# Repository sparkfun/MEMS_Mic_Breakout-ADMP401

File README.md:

**NOTE:** *This product has been retired from our catalog due to the IC being EOL. We recommend checking out the [ICS-40180](https://www.sparkfun.com/products/18011) as an alternative. While the ICS-40180 has similar characteristics, note that the footprint is different than the ADMP401. If you are looking for more up-to-date info, please check out the following resource to see how other users are still hacking and improving on this product.*

* *[SparkFun Forum](https://forum.sparkfun.com/)*

SparkFun MEMS Microphone Breakout - INMP401 (ADMP401)
===================================================

[*SparkFun MEMS Microphone Breakout - INMP401 (ADMP401) (BOB-09868)*](https://www.sparkfun.com/products/9868)

This tiny breakout board features the ADMP401 MEMs microphone.

Repository Contents
-------------------
* **/Firmware** - Example Arduino Sketches 
* **/Hardware** - All Eagle design files (.brd, .sch)

Documentation
--------------
* **[Hookup Guide](https://learn.sparkfun.com/tutorials/mems-microphone-hookup-guide)** - Basic hookup guide.

License Information
-------------------
The hardware is released under [Creative Commons ShareAlike 4.0 International](https://creativecommons.org/licenses/by-sa/4.0/).
The code is beerware; if you see me (or any other SparkFun employee) at the local, and you've found our code helpful, please buy us a round!

Distributed as-is; no warranty is given.

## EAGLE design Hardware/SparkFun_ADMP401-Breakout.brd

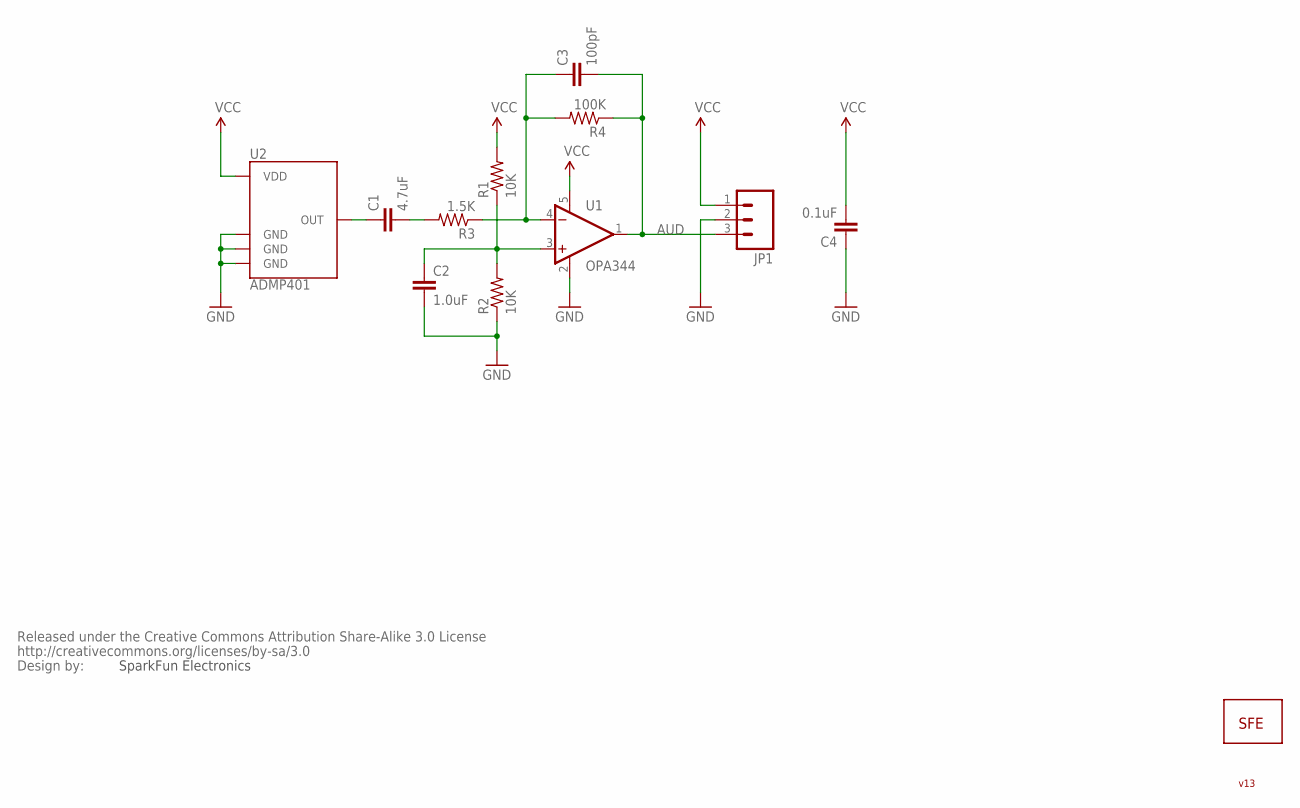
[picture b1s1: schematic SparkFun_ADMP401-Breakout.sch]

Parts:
C1: 4.7uF; 0402-CAP
C2: 1.0uF; 0402-CAP
C3: 100pF; 0402-CAP
C4: 0.1uF; 0402-CAP
JP1: M03PTH; 1X03
R1, R2: 10K; 0402-RES
R3: 1.5K; 0402-RES
R4: 100K; 0402-RES
U1: OPA344; SOT23-5
U2: ADMP401
U$1: LOGO-SFESK; SFE-LOGO-FLAME
U$2: CREATIVE_COMMONS

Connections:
AUD: C3.2, JP1.3, R4.1, U1.1 (OUT)
GND: C2.2, C4.1, JP1.2, R2.1, U1.2 (V-), U2.2 (GND), U2.4 (GND), U2.6 (GND)
unnamed: C1.1, U2.1 (OUT)
unnamed: C3.1, R3.1, R4.2, U1.4 (-IN)
unnamed: C1.2, R3.2
unnamed: C2.1, R1.1, R2.2, U1.3 (+IN)
VCC: C4.2, JP1.1, R1.2, U1.5 (V+), U2.5 (VDD)

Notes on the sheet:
SparkFun Electronics
v13

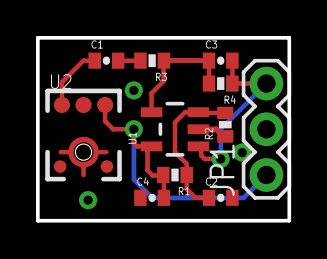
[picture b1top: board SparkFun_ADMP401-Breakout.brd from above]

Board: 2 copper layers, 14.0 x 10.2 mm, 13 parts (1 on the bottom side), 7 nets.

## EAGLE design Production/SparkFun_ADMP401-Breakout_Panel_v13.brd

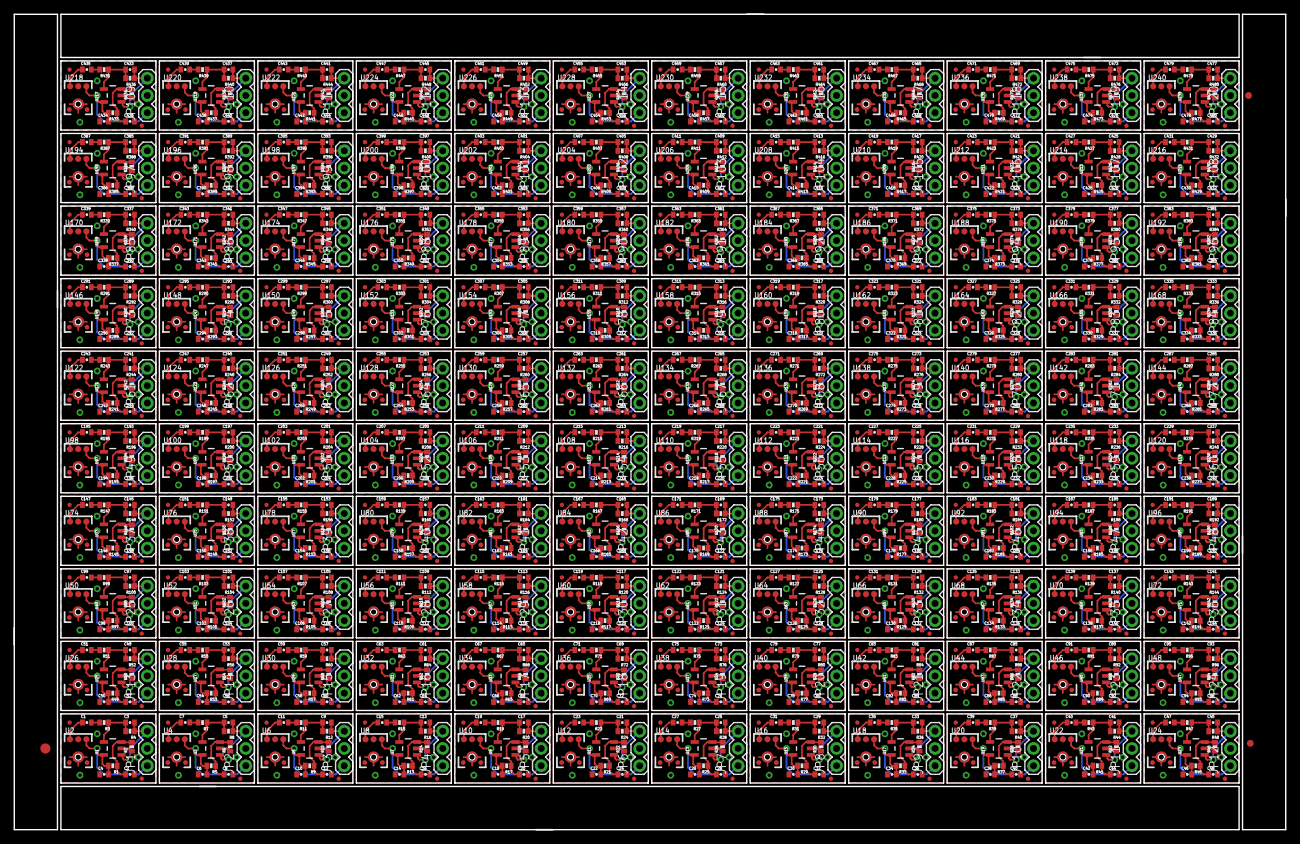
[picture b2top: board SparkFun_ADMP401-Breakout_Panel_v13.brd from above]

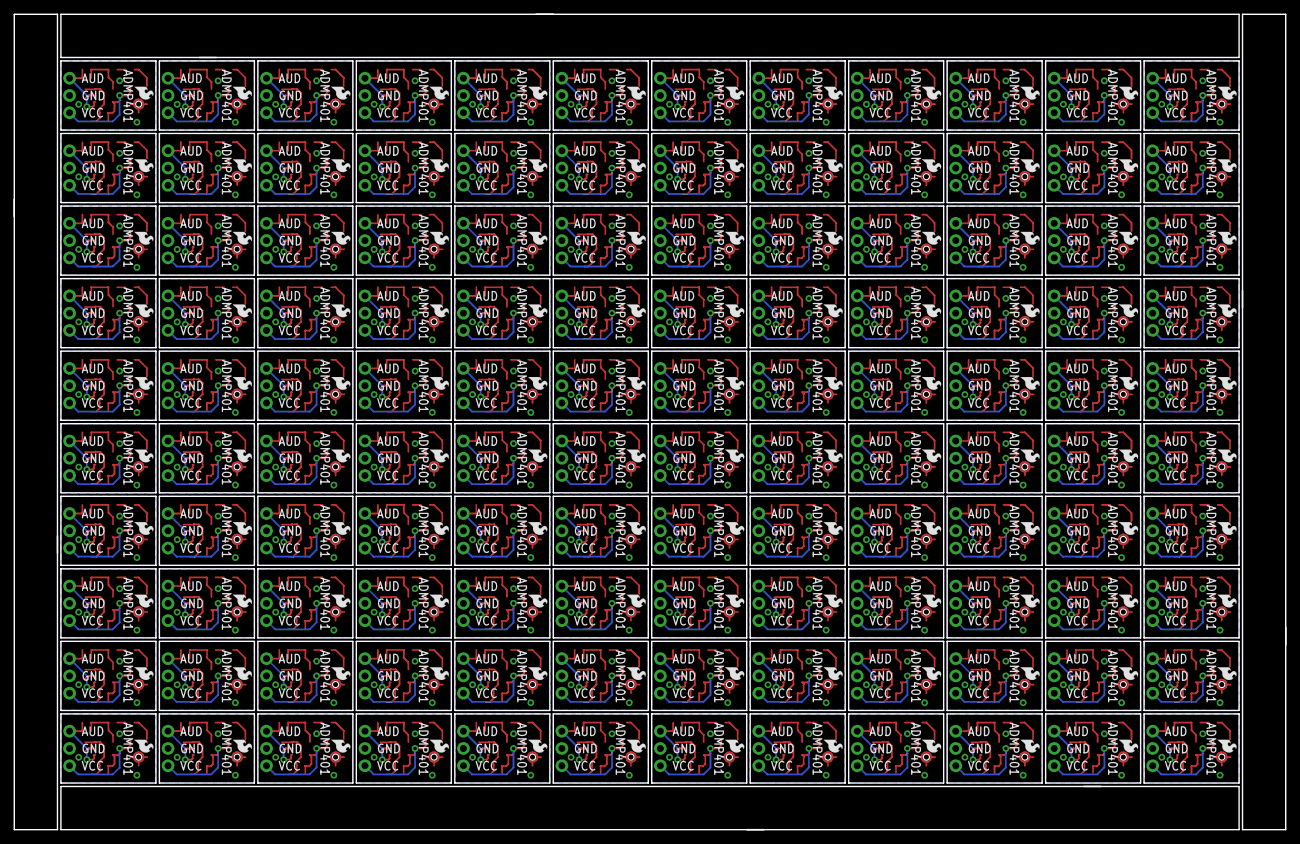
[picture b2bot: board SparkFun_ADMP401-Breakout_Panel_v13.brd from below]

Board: 2 copper layers, 186.9 x 119.9 mm, 1683 parts (120 on the bottom side), 840 nets.

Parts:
C1, C7, C11, C15, C19, C23, C27, C31, C35, C39, C43, C47, C51, C55, C59, C63, C67, C71, C75, C79, C83, C87, C91, C95, C99, C103, C107, C111, C115, C119, C123, C127, C131, C135, C139, C143, C147, C151, C155, C159, C163, C167, C171, C175, C179, C183, C187, C191, C195, C199, C203, C207, C211, C215, C219, C223, C227, C231, C235, C239, C243, C247, C251, C255, C259, C263, C267, C271, C275, C279, C283, C287, C291, C295, C299, C303, C307, C311, C315, C319, C323, C327, C331, C335, C339, C343, C347, C351, C355, C359, C363, C367, C371, C375, C379, C383, C387, C391, C395, C399, C403, C407, C411, C415, C419, C423, C427, C431, C435, C439, C443, C447, C451, C455, C459, C463, C467, C471, C475, C479: 4.7uF; 0402-CAP
C2, C8, C12, C16, C20, C24, C28, C32, C36, C40, C44, C48, C52, C56, C60, C64, C68, C72, C76, C80, C84, C88, C92, C96, C100, C104, C108, C112, C116, C120, C124, C128, C132, C136, C140, C144, C148, C152, C156, C160, C164, C168, C172, C176, C180, C184, C188, C192, C196, C200, C204, C208, C212, C216, C220, C224, C228, C232, C236, C240, C244, C248, C252, C256, C260, C264, C268, C272, C276, C280, C284, C288, C292, C296, C300, C304, C308, C312, C316, C320, C324, C328, C332, C336, C340, C344, C348, C352, C356, C360, C364, C368, C372, C376, C380, C384, C388, C392, C396, C400, C404, C408, C412, C416, C420, C424, C428, C432, C436, C440, C444, C448, C452, C456, C460, C464, C468, C472, C476, C480: 1.0uF; 0402-CAP
C3, C5, C9, C13, C17, C21, C25, C29, C33, C37, C41, C45, C49, C53, C57, C61, C65, C69, C73, C77, C81, C85, C89, C93, C97, C101, C105, C109, C113, C117, C121, C125, C129, C133, C137, C141, C145, C149, C153, C157, C161, C165, C169, C173, C177, C181, C185, C189, C193, C197, C201, C205, C209, C213, C217, C221, C225, C229, C233, C237, C241, C245, C249, C253, C257, C261, C265, C269, C273, C277, C281, C285, C289, C293, C297, C301, C305, C309, C313, C317, C321, C325, C329, C333, C337, C341, C345, C349, C353, C357, C361, C365, C369, C373, C377, C381, C385, C389, C393, C397, C401, C405, C409, C413, C417, C421, C425, C429, C433, C437, C441, C445, C449, C453, C457, C461, C465, C469, C473, C477: 100pF; 0402-CAP
C4, C6, C10, C14, C18, C22, C26, C30, C34, C38, C42, C46, C50, C54, C58, C62, C66, C70, C74, C78, C82, C86, C90, C94, C98, C102, C106, C110, C114, C118, C122, C126, C130, C134, C138, C142, C146, C150, C154, C158, C162, C166, C170, C174, C178, C182, C186, C190, C194, C198, C202, C206, C210, C214, C218, C222, C226, C230, C234, C238, C242, C246, C250, C254, C258, C262, C266, C270, C274, C278, C282, C286, C290, C294, C298, C302, C306, C310, C314, C318, C322, C326, C330, C334, C338, C342, C346, C350, C354, C358, C362, C366, C370, C374, C378, C382, C386, C390, C394, C398, C402, C406, C410, C414, C418, C422, C426, C430, C434, C438, C442, C446, C450, C454, C458, C462, C466, C470, C474, C478: 0.1uF; 0402-CAP
E$1, E$2, E$3, E$4, E$5, E$6, E$7, E$8, E$9, E$10, E$11, E$12, E$13, E$14, E$15, E$16, E$17, E$18, E$19, E$20, E$21, E$22, E$23, E$24, E$25, E$26, E$27, E$28, E$29, E$30, E$31, E$32, E$33, E$34, E$35, E$36, E$37, E$38, E$39, E$40, E$41, E$42, E$43, E$44, E$45, E$46, E$47, E$48, E$49, E$50, E$51, E$52, E$53, E$54, E$55, E$56, E$57, E$58, E$59, E$60, E$61, E$62, E$63, E$64, E$65, E$66, E$67, E$68, E$69, E$70, E$71, E$72, E$73, E$74, E$75, E$76, E$77, E$78, E$79, E$80, E$81, E$82, E$83, E$84, E$85, E$86, E$87, E$88, E$89, E$90, E$91, E$92, E$93, E$94, E$95, E$96, E$97, E$98, E$99, E$100, E$101, E$102, E$103, E$104, E$105, E$106, E$107, E$108, E$109, E$110, E$111, E$112, E$113, E$114, E$115, E$116, E$117, E$118, E$119, E$120, E$121, E$122, E$123, E$124, E$125, E$126, E$127, E$128, E$129, E$130, E$131, E$132, E$133, E$134, E$135, E$136, E$137, E$138, E$139, E$140, E$141, E$142, E$143, E$144, E$145, E$146, E$147, E$148, E$149, E$150, E$151, E$152, E$153, E$154, E$155, E$156, E$157, E$158, E$159, E$160, E$161, E$162, E$163, E$164, E$165, E$166, E$167, E$168, E$169, E$170, E$171, E$172, E$173, E$174, E$175, E$176, E$177, E$178, E$179, E$180, E$181, E$182, E$183, E$184, E$185, E$186, E$187, E$188, E$189, E$190, E$191, E$192, E$193, E$194, E$195, E$196, E$197, E$198, E$199, E$200, E$201, E$202, E$203, E$204, E$205, E$206, E$207, E$208, E$209, E$210, E$211, E$212, E$213, E$214, E$215, E$216, E$217, E$218, E$219, E$220, E$221, E$222, E$223, E$224, E$225, E$226, E$227, E$228, E$229, E$230, E$231, E$232, E$233, E$234, E$235, E$236, E$237, E$238, E$239, E$240: MICRO-FIDUCIAL
E$241: FIDUCIAL-1.5X3
E$247, E$248: FIDUCIAL-1X2
JP1, JP2, JP3, JP4, JP5, JP6, JP7, JP8, JP9, JP10, JP11, JP12, JP13, JP14, JP15, JP16, JP17, JP18, JP19, JP20, JP21, JP22, JP23, JP24, JP25, JP26, JP27, JP28, JP29, JP30, JP31, JP32, JP33, JP34, JP35, JP36, JP37, JP38, JP39, JP40, JP41, JP42, JP43, JP44, JP45, JP46, JP47, JP48, JP49, JP50, JP51, JP52, JP53, JP54, JP55, JP56, JP57, JP58, JP59, JP60, JP61, JP62, JP63, JP64, JP65, JP66, JP67, JP68, JP69, JP70, JP71, JP72, JP73, JP74, JP75, JP76, JP77, JP78, JP79, JP80, JP81, JP82, JP83, JP84, JP85, JP86, JP87, JP88, JP89, JP90, JP91, JP92, JP93, JP94, JP95, JP96, JP97, JP98, JP99, JP100, JP101, JP102, JP103, JP104, JP105, JP106, JP107, JP108, JP109, JP110, JP111, JP112, JP113, JP114, JP115, JP116, JP117, JP118, JP119, JP120: 1X03
R1, R2, R5, R6, R9, R10, R13, R14, R17, R18, R21, R22, R25, R26, R29, R30, R33, R34, R37, R38, R41, R42, R45, R46, R49, R50, R53, R54, R57, R58, R61, R62, R65, R66, R69, R70, R73, R74, R77, R78, R81, R82, R85, R86, R89, R90, R93, R94, R97, R98, R101, R102, R105, R106, R109, R110, R113, R114, R117, R118, R121, R122, R125, R126, R129, R130, R133, R134, R137, R138, R141, R142, R145, R146, R149, R150, R153, R154, R157, R158, R161, R162, R165, R166, R169, R170, R173, R174, R177, R178, R181, R182, R185, R186, R189, R190, R193, R194, R197, R198, R201, R202, R205, R206, R209, R210, R213, R214, R217, R218, R221, R222, R225, R226, R229, R230, R233, R234, R237, R238, R241, R242, R245, R246, R249, R250, R253, R254, R257, R258, R261, R262, R265, R266, R269, R270, R273, R274, R277, R278, R281, R282, R285, R286, R289, R290, R293, R294, R297, R298, R301, R302, R305, R306, R309, R310, R313, R314, R317, R318, R321, R322, R325, R326, R329, R330, R333, R334, R337, R338, R341, R342, R345, R346, R349, R350, R353, R354, R357, R358, R361, R362, R365, R366, R369, R370, R373, R374, R377, R378, R381, R382, R385, R386, R389, R390, R393, R394, R397, R398, R401, R402, R405, R406, R409, R410, R413, R414, R417, R418, R421, R422, R425, R426, R429, R430, R433, R434, R437, R438, R441, R442, R445, R446, R449, R450, R453, R454, R457, R458, R461, R462, R465, R466, R469, R470, R473, R474, R477, R478: 10K; 0402-RES
R3, R7, R11, R15, R19, R23, R27, R31, R35, R39, R43, R47, R51, R55, R59, R63, R67, R71, R75, R79, R83, R87, R91, R95, R99, R103, R107, R111, R115, R119, R123, R127, R131, R135, R139, R143, R147, R151, R155, R159, R163, R167, R171, R175, R179, R183, R187, R191, R195, R199, R203, R207, R211, R215, R219, R223, R227, R231, R235, R239, R243, R247, R251, R255, R259, R263, R267, R271, R275, R279, R283, R287, R291, R295, R299, R303, R307, R311, R315, R319, R323, R327, R331, R335, R339, R343, R347, R351, R355, R359, R363, R367, R371, R375, R379, R383, R387, R391, R395, R399, R403, R407, R411, R415, R419, R423, R427, R431, R435, R439, R443, R447, R451, R455, R459, R463, R467, R471, R475, R479: 1.5K; 0402-RES
R4, R8, R12, R16, R20, R24, R28, R32, R36, R40, R44, R48, R52, R56, R60, R64, R68, R72, R76, R80, R84, R88, R92, R96, R100, R104, R108, R112, R116, R120, R124, R128, R132, R136, R140, R144, R148, R152, R156, R160, R164, R168, R172, R176, R180, R184, R188, R192, R196, R200, R204, R208, R212, R216, R220, R224, R228, R232, R236, R240, R244, R248, R252, R256, R260, R264, R268, R272, R276, R280, R284, R288, R292, R296, R300, R304, R308, R312, R316, R320, R324, R328, R332, R336, R340, R344, R348, R352, R356, R360, R364, R368, R372, R376, R380, R384, R388, R392, R396, R400, R404, R408, R412, R416, R420, R424, R428, R432, R436, R440, R444, R448, R452, R456, R460, R464, R468, R472, R476, R480: 100K; 0402-RES
U1, U3, U5, U7, U9, U11, U13, U15, U17, U19, U21, U23, U25, U27, U29, U31, U33, U35, U37, U39, U41, U43, U45, U47, U49, U51, U53, U55, U57, U59, U61, U63, U65, U67, U69, U71, U73, U75, U77, U79, U81, U83, U85, U87, U89, U91, U93, U95, U97, U99, U101, U103, U105, U107, U109, U111, U113, U115, U117, U119, U121, U123, U125, U127, U129, U131, U133, U135, U137, U139, U141, U143, U145, U147, U149, U151, U153, U155, U157, U159, U161, U163, U165, U167, U169, U171, U173, U175, U177, U179, U181, U183, U185, U187, U189, U191, U193, U195, U197, U199, U201, U203, U205, U207, U209, U211, U213, U215, U217, U219, U221, U223, U225, U227, U229, U231, U233, U235, U237, U239: OPA344; SOT23-5
U2, U4, U6, U8, U10, U12, U14, U16, U18, U20, U22, U24, U26, U28, U30, U32, U34, U36, U38, U40, U42, U44, U46, U48, U50, U52, U54, U56, U58, U60, U62, U64, U66, U68, U70, U72, U74, U76, U78, U80, U82, U84, U86, U88, U90, U92, U94, U96, U98, U100, U102, U104, U106, U108, U110, U112, U114, U116, U118, U120, U122, U124, U126, U128, U130, U132, U134, U136, U138, U140, U142, U144, U146, U148, U150, U152, U154, U156, U158, U160, U162, U164, U166, U168, U170, U172, U174, U176, U178, U180, U182, U184, U186, U188, U190, U192, U194, U196, U198, U200, U202, U204, U206, U208, U210, U212, U214, U216, U218, U220, U222, U224, U226, U228, U230, U232, U234, U236, U238, U240: ADMP401
U$1, U$2, U$3, U$4, U$5, U$6, U$7, U$8, U$9, U$10, U$11, U$12, U$13, U$14, U$15, U$16, U$17, U$18, U$19, U$20, U$21, U$22, U$23, U$24, U$25, U$26, U$27, U$28, U$29, U$30, U$31, U$32, U$33, U$34, U$35, U$36, U$37, U$38, U$39, U$40, U$41, U$42, U$43, U$44, U$45, U$46, U$47, U$48, U$49, U$50, U$51, U$52, U$53, U$54, U$55, U$56, U$57, U$58, U$59, U$60, U$61, U$62, U$63, U$64, U$65, U$66, U$67, U$68, U$69, U$70, U$71, U$72, U$73, U$74, U$75, U$76, U$77, U$78, U$79, U$80, U$81, U$82, U$83, U$84, U$85, U$86, U$87, U$88, U$89, U$90, U$91, U$92, U$93, U$94, U$95, U$96, U$97, U$98, U$99, U$100, U$101, U$102, U$103, U$104, U$105, U$106, U$107, U$108, U$109, U$110, U$111, U$112, U$113, U$114, U$115, U$116, U$117, U$118, U$119, U$120: LOGO-SFESK; SFE-LOGO-FLAME

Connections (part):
AUD: C3.2, JP1.3, R4.1, U1.1
AUD1: C5.2, JP2.3, R8.1, U3.1
AUD2: C9.2, JP3.3, R12.1, U5.1
AUD3: C13.2, JP4.3, R16.1, U7.1
AUD4: C17.2, JP5.3, R20.1, U9.1
AUD5: C21.2, JP6.3, R24.1, U11.1
AUD6: C25.2, JP7.3, R28.1, U13.1
AUD7: C29.2, JP8.3, R32.1, U15.1
AUD8: C33.2, JP9.3, R36.1, U17.1
AUD9: C37.2, JP10.3, R40.1, U19.1
AUD10: C41.2, JP11.3, R44.1, U21.1
AUD11: C45.2, JP12.3, R48.1, U23.1
AUD12: C49.2, JP13.3, R52.1, U25.1
AUD13: C53.2, JP14.3, R56.1, U27.1
AUD14: C57.2, JP15.3, R60.1, U29.1
AUD15: C61.2, JP16.3, R64.1, U31.1
AUD16: C65.2, JP17.3, R68.1, U33.1
AUD17: C69.2, JP18.3, R72.1, U35.1
AUD18: C73.2, JP19.3, R76.1, U37.1
AUD19: C77.2, JP20.3, R80.1, U39.1
AUD20: C81.2, JP21.3, R84.1, U41.1
AUD21: C85.2, JP22.3, R88.1, U43.1
AUD22: C89.2, JP23.3, R92.1, U45.1
AUD23: C93.2, JP24.3, R96.1, U47.1
AUD24: C97.2, JP25.3, R100.1, U49.1
AUD25: C101.2, JP26.3, R104.1, U51.1
AUD26: C105.2, JP27.3, R108.1, U53.1
AUD27: C109.2, JP28.3, R112.1, U55.1
AUD28: C113.2, JP29.3, R116.1, U57.1
AUD29: C117.2, JP30.3, R120.1, U59.1
AUD30: C121.2, JP31.3, R124.1, U61.1
AUD31: C125.2, JP32.3, R128.1, U63.1
AUD32: C129.2, JP33.3, R132.1, U65.1
AUD33: C133.2, JP34.3, R136.1, U67.1
AUD34: C137.2, JP35.3, R140.1, U69.1
AUD35: C141.2, JP36.3, R144.1, U71.1
AUD36: C145.2, JP37.3, R148.1, U73.1
AUD37: C149.2, JP38.3, R152.1, U75.1
AUD38: C153.2, JP39.3, R156.1, U77.1
AUD39: C157.2, JP40.3, R160.1, U79.1
AUD40: C161.2, JP41.3, R164.1, U81.1
AUD41: C165.2, JP42.3, R168.1, U83.1
AUD42: C169.2, JP43.3, R172.1, U85.1
AUD43: C173.2, JP44.3, R176.1, U87.1
AUD44: C177.2, JP45.3, R180.1, U89.1
AUD45: C181.2, JP46.3, R184.1, U91.1
AUD46: C185.2, JP47.3, R188.1, U93.1
AUD47: C189.2, JP48.3, R192.1, U95.1
AUD48: C193.2, JP49.3, R196.1, U97.1
AUD49: C197.2, JP50.3, R200.1, U99.1
AUD50: C201.2, JP51.3, R204.1, U101.1
AUD51: C205.2, JP52.3, R208.1, U103.1
AUD52: C209.2, JP53.3, R212.1, U105.1
AUD53: C213.2, JP54.3, R216.1, U107.1
AUD54: C217.2, JP55.3, R220.1, U109.1
AUD55: C221.2, JP56.3, R224.1, U111.1
AUD56: C225.2, JP57.3, R228.1, U113.1
AUD57: C229.2, JP58.3, R232.1, U115.1
AUD58: C233.2, JP59.3, R236.1, U117.1
AUD59: C237.2, JP60.3, R240.1, U119.1
AUD60: C241.2, JP61.3, R244.1, U121.1
AUD61: C245.2, JP62.3, R248.1, U123.1
AUD62: C249.2, JP63.3, R252.1, U125.1
AUD63: C253.2, JP64.3, R256.1, U127.1
AUD64: C257.2, JP65.3, R260.1, U129.1
AUD65: C261.2, JP66.3, R264.1, U131.1
AUD66: C265.2, JP67.3, R268.1, U133.1
AUD67: C269.2, JP68.3, R272.1, U135.1
AUD68: C273.2, JP69.3, R276.1, U137.1
AUD69: C277.2, JP70.3, R280.1, U139.1
AUD70: C281.2, JP71.3, R284.1, U141.1
AUD71: C285.2, JP72.3, R288.1, U143.1
AUD72: C289.2, JP73.3, R292.1, U145.1
AUD73: C293.2, JP74.3, R296.1, U147.1
AUD74: C297.2, JP75.3, R300.1, U149.1
AUD75: C301.2, JP76.3, R304.1, U151.1
AUD76: C305.2, JP77.3, R308.1, U153.1
AUD77: C309.2, JP78.3, R312.1, U155.1
AUD78: C313.2, JP79.3, R316.1, U157.1
AUD79: C317.2, JP80.3, R320.1, U159.1
AUD80: C321.2, JP81.3, R324.1, U161.1
AUD81: C325.2, JP82.3, R328.1, U163.1
AUD82: C329.2, JP83.3, R332.1, U165.1
AUD83: C333.2, JP84.3, R336.1, U167.1
AUD84: C337.2, JP85.3, R340.1, U169.1
AUD85: C341.2, JP86.3, R344.1, U171.1
AUD86: C345.2, JP87.3, R348.1, U173.1
AUD87: C349.2, JP88.3, R352.1, U175.1
AUD88: C353.2, JP89.3, R356.1, U177.1
AUD89: C357.2, JP90.3, R360.1, U179.1
AUD90: C361.2, JP91.3, R364.1, U181.1
AUD91: C365.2, JP92.3, R368.1, U183.1
AUD92: C369.2, JP93.3, R372.1, U185.1
AUD93: C373.2, JP94.3, R376.1, U187.1
AUD94: C377.2, JP95.3, R380.1, U189.1
AUD95: C381.2, JP96.3, R384.1, U191.1
AUD96: C385.2, JP97.3, R388.1, U193.1
AUD97: C389.2, JP98.3, R392.1, U195.1
AUD98: C393.2, JP99.3, R396.1, U197.1
AUD99: C397.2, JP100.3, R400.1, U199.1
AUD100: C401.2, JP101.3, R404.1, U201.1
AUD101: C405.2, JP102.3, R408.1, U203.1
AUD102: C409.2, JP103.3, R412.1, U205.1
AUD103: C413.2, JP104.3, R416.1, U207.1
AUD104: C417.2, JP105.3, R420.1, U209.1
AUD105: C421.2, JP106.3, R424.1, U211.1
AUD106: C425.2, JP107.3, R428.1, U213.1
AUD107: C429.2, JP108.3, R432.1, U215.1
AUD108: C433.2, JP109.3, R436.1, U217.1
AUD109: C437.2, JP110.3, R440.1, U219.1
AUD110: C441.2, JP111.3, R444.1, U221.1
AUD111: C445.2, JP112.3, R448.1, U223.1
AUD112: C449.2, JP113.3, R452.1, U225.1
AUD113: C453.2, JP114.3, R456.1, U227.1
AUD114: C457.2, JP115.3, R460.1, U229.1
AUD115: C461.2, JP116.3, R464.1, U231.1
AUD116: C465.2, JP117.3, R468.1, U233.1
AUD117: C469.2, JP118.3, R472.1, U235.1
AUD118: C473.2, JP119.3, R476.1, U237.1
AUD119: C477.2, JP120.3, R480.1, U239.1
GND: C2.2, C4.1, JP1.2, R2.1, U1.2, U2.2, U2.4, U2.6
GND1: C6.1, C8.2, JP2.2, R6.1, U3.2, U4.2, U4.4, U4.6
GND2: C10.1, C12.2, JP3.2, R10.1, U5.2, U6.2, U6.4, U6.6
GND3: C14.1, C16.2, JP4.2, R14.1, U7.2, U8.2, U8.4, U8.6
GND4: C18.1, C20.2, JP5.2, R18.1, U9.2, U10.2, U10.4, U10.6
GND5: C22.1, C24.2, JP6.2, R22.1, U11.2, U12.2, U12.4, U12.6
GND6: C26.1, C28.2, JP7.2, R26.1, U13.2, U14.2, U14.4, U14.6
GND7: C30.1, C32.2, JP8.2, R30.1, U15.2, U16.2, U16.4, U16.6
GND8: C34.1, C36.2, JP9.2, R34.1, U17.2, U18.2, U18.4, U18.6
GND9: C38.1, C40.2, JP10.2, R38.1, U19.2, U20.2, U20.4, U20.6
GND10: C42.1, C44.2, JP11.2, R42.1, U21.2, U22.2, U22.4, U22.6
GND11: C46.1, C48.2, JP12.2, R46.1, U23.2, U24.2, U24.4, U24.6
GND12: C50.1, C52.2, JP13.2, R50.1, U25.2, U26.2, U26.4, U26.6
GND13: C54.1, C56.2, JP14.2, R54.1, U27.2, U28.2, U28.4, U28.6
GND14: C58.1, C60.2, JP15.2, R58.1, U29.2, U30.2, U30.4, U30.6
GND15: C62.1, C64.2, JP16.2, R62.1, U31.2, U32.2, U32.4, U32.6
GND16: C66.1, C68.2, JP17.2, R66.1, U33.2, U34.2, U34.4, U34.6
GND17: C70.1, C72.2, JP18.2, R70.1, U35.2, U36.2, U36.4, U36.6
GND18: C74.1, C76.2, JP19.2, R74.1, U37.2, U38.2, U38.4, U38.6
GND19: C78.1, C80.2, JP20.2, R78.1, U39.2, U40.2, U40.4, U40.6
GND20: C82.1, C84.2, JP21.2, R82.1, U41.2, U42.2, U42.4, U42.6
GND21: C86.1, C88.2, JP22.2, R86.1, U43.2, U44.2, U44.4, U44.6
GND22: C90.1, C92.2, JP23.2, R90.1, U45.2, U46.2, U46.4, U46.6
GND23: C94.1, C96.2, JP24.2, R94.1, U47.2, U48.2, U48.4, U48.6
GND24: C98.1, C100.2, JP25.2, R98.1, U49.2, U50.2, U50.4, U50.6
GND25: C102.1, C104.2, JP26.2, R102.1, U51.2, U52.2, U52.4, U52.6
GND26: C106.1, C108.2, JP27.2, R106.1, U53.2, U54.2, U54.4, U54.6
GND27: C110.1, C112.2, JP28.2, R110.1, U55.2, U56.2, U56.4, U56.6
GND28: C114.1, C116.2, JP29.2, R114.1, U57.2, U58.2, U58.4, U58.6
GND29: C118.1, C120.2, JP30.2, R118.1, U59.2, U60.2, U60.4, U60.6
GND30: C122.1, C124.2, JP31.2, R122.1, U61.2, U62.2, U62.4, U62.6
GND31: C126.1, C128.2, JP32.2, R126.1, U63.2, U64.2, U64.4, U64.6
GND32: C130.1, C132.2, JP33.2, R130.1, U65.2, U66.2, U66.4, U66.6
GND33: C134.1, C136.2, JP34.2, R134.1, U67.2, U68.2, U68.4, U68.6
GND34: C138.1, C140.2, JP35.2, R138.1, U69.2, U70.2, U70.4, U70.6
GND35: C142.1, C144.2, JP36.2, R142.1, U71.2, U72.2, U72.4, U72.6
GND36: C146.1, C148.2, JP37.2, R146.1, U73.2, U74.2, U74.4, U74.6
GND37: C150.1, C152.2, JP38.2, R150.1, U75.2, U76.2, U76.4, U76.6
GND38: C154.1, C156.2, JP39.2, R154.1, U77.2, U78.2, U78.4, U78.6
GND39: C158.1, C160.2, JP40.2, R158.1, U79.2, U80.2, U80.4, U80.6
GND40: C162.1, C164.2, JP41.2, R162.1, U81.2, U82.2, U82.4, U82.6
GND41: C166.1, C168.2, JP42.2, R166.1, U83.2, U84.2, U84.4, U84.6
GND42: C170.1, C172.2, JP43.2, R170.1, U85.2, U86.2, U86.4, U86.6
GND43: C174.1, C176.2, JP44.2, R174.1, U87.2, U88.2, U88.4, U88.6
GND44: C178.1, C180.2, JP45.2, R178.1, U89.2, U90.2, U90.4, U90.6
GND45: C182.1, C184.2, JP46.2, R182.1, U91.2, U92.2, U92.4, U92.6
GND46: C186.1, C188.2, JP47.2, R186.1, U93.2, U94.2, U94.4, U94.6
GND47: C190.1, C192.2, JP48.2, R190.1, U95.2, U96.2, U96.4, U96.6
GND48: C194.1, C196.2, JP49.2, R194.1, U97.2, U98.2, U98.4, U98.6
GND49: C198.1, C200.2, JP50.2, R198.1, U99.2, U100.2, U100.4, U100.6
GND50: C202.1, C204.2, JP51.2, R202.1, U101.2, U102.2, U102.4, U102.6
GND51: C206.1, C208.2, JP52.2, R206.1, U103.2, U104.2, U104.4, U104.6
GND52: C210.1, C212.2, JP53.2, R210.1, U105.2, U106.2, U106.4, U106.6
GND53: C214.1, C216.2, JP54.2, R214.1, U107.2, U108.2, U108.4, U108.6
GND54: C218.1, C220.2, JP55.2, R218.1, U109.2, U110.2, U110.4, U110.6
GND55: C222.1, C224.2, JP56.2, R222.1, U111.2, U112.2, U112.4, U112.6
GND56: C226.1, C228.2, JP57.2, R226.1, U113.2, U114.2, U114.4, U114.6
GND57: C230.1, C232.2, JP58.2, R230.1, U115.2, U116.2, U116.4, U116.6
GND58: C234.1, C236.2, JP59.2, R234.1, U117.2, U118.2, U118.4, U118.6
GND59: C238.1, C240.2, JP60.2, R238.1, U119.2, U120.2, U120.4, U120.6
GND60: C242.1, C244.2, JP61.2, R242.1, U121.2, U122.2, U122.4, U122.6
GND61: C246.1, C248.2, JP62.2, R246.1, U123.2, U124.2, U124.4, U124.6
GND62: C250.1, C252.2, JP63.2, R250.1, U125.2, U126.2, U126.4, U126.6
GND63: C254.1, C256.2, JP64.2, R254.1, U127.2, U128.2, U128.4, U128.6
GND64: C258.1, C260.2, JP65.2, R258.1, U129.2, U130.2, U130.4, U130.6
GND65: C262.1, C264.2, JP66.2, R262.1, U131.2, U132.2, U132.4, U132.6
GND66: C266.1, C268.2, JP67.2, R266.1, U133.2, U134.2, U134.4, U134.6
GND67: C270.1, C272.2, JP68.2, R270.1, U135.2, U136.2, U136.4, U136.6
GND68: C274.1, C276.2, JP69.2, R274.1, U137.2, U138.2, U138.4, U138.6
GND69: C278.1, C280.2, JP70.2, R278.1, U139.2, U140.2, U140.4, U140.6
GND70: C282.1, C284.2, JP71.2, R282.1, U141.2, U142.2, U142.4, U142.6
GND71: C286.1, C288.2, JP72.2, R286.1, U143.2, U144.2, U144.4, U144.6
GND72: C290.1, C292.2, JP73.2, R290.1, U145.2, U146.2, U146.4, U146.6
GND73: C294.1, C296.2, JP74.2, R294.1, U147.2, U148.2, U148.4, U148.6
GND74: C298.1, C300.2, JP75.2, R298.1, U149.2, U150.2, U150.4, U150.6
GND75: C302.1, C304.2, JP76.2, R302.1, U151.2, U152.2, U152.4, U152.6
GND76: C306.1, C308.2, JP77.2, R306.1, U153.2, U154.2, U154.4, U154.6
GND77: C310.1, C312.2, JP78.2, R310.1, U155.2, U156.2, U156.4, U156.6
GND78: C314.1, C316.2, JP79.2, R314.1, U157.2, U158.2, U158.4, U158.6
GND79: C318.1, C320.2, JP80.2, R318.1, U159.2, U160.2, U160.4, U160.6
GND80: C322.1, C324.2, JP81.2, R322.1, U161.2, U162.2, U162.4, U162.6
GND81: C326.1, C328.2, JP82.2, R326.1, U163.2, U164.2, U164.4, U164.6
GND82: C330.1, C332.2, JP83.2, R330.1, U165.2, U166.2, U166.4, U166.6
GND83: C334.1, C336.2, JP84.2, R334.1, U167.2, U168.2, U168.4, U168.6
GND84: C338.1, C340.2, JP85.2, R338.1, U169.2, U170.2, U170.4, U170.6
GND85: C342.1, C344.2, JP86.2, R342.1, U171.2, U172.2, U172.4, U172.6
GND86: C346.1, C348.2, JP87.2, R346.1, U173.2, U174.2, U174.4, U174.6
GND87: C350.1, C352.2, JP88.2, R350.1, U175.2, U176.2, U176.4, U176.6
GND88: C354.1, C356.2, JP89.2, R354.1, U177.2, U178.2, U178.4, U178.6
GND89: C358.1, C360.2, JP90.2, R358.1, U179.2, U180.2, U180.4, U180.6
GND90: C362.1, C364.2, JP91.2, R362.1, U181.2, U182.2, U182.4, U182.6
GND91: C366.1, C368.2, JP92.2, R366.1, U183.2, U184.2, U184.4, U184.6
GND92: C370.1, C372.2, JP93.2, R370.1, U185.2, U186.2, U186.4, U186.6
GND93: C374.1, C376.2, JP94.2, R374.1, U187.2, U188.2, U188.4, U188.6
GND94: C378.1, C380.2, JP95.2, R378.1, U189.2, U190.2, U190.4, U190.6
GND95: C382.1, C384.2, JP96.2, R382.1, U191.2, U192.2, U192.4, U192.6
GND96: C386.1, C388.2, JP97.2, R386.1, U193.2, U194.2, U194.4, U194.6
GND97: C390.1, C392.2, JP98.2, R390.1, U195.2, U196.2, U196.4, U196.6
GND98: C394.1, C396.2, JP99.2, R394.1, U197.2, U198.2, U198.4, U198.6
GND99: C398.1, C400.2, JP100.2, R398.1, U199.2, U200.2, U200.4, U200.6
GND100: C402.1, C404.2, JP101.2, R402.1, U201.2, U202.2, U202.4, U202.6
GND101: C406.1, C408.2, JP102.2, R406.1, U203.2, U204.2, U204.4, U204.6
GND102: C410.1, C412.2, JP103.2, R410.1, U205.2, U206.2, U206.4, U206.6
GND103: C414.1, C416.2, JP104.2, R414.1, U207.2, U208.2, U208.4, U208.6
GND104: C418.1, C420.2, JP105.2, R418.1, U209.2, U210.2, U210.4, U210.6
GND105: C422.1, C424.2, JP106.2, R422.1, U211.2, U212.2, U212.4, U212.6
GND106: C426.1, C428.2, JP107.2, R426.1, U213.2, U214.2, U214.4, U214.6
GND107: C430.1, C432.2, JP108.2, R430.1, U215.2, U216.2, U216.4, U216.6
GND108: C434.1, C436.2, JP109.2, R434.1, U217.2, U218.2, U218.4, U218.6
GND109: C438.1, C440.2, JP110.2, R438.1, U219.2, U220.2, U220.4, U220.6
GND110: C442.1, C444.2, JP111.2, R442.1, U221.2, U222.2, U222.4, U222.6
GND111: C446.1, C448.2, JP112.2, R446.1, U223.2, U224.2, U224.4, U224.6
GND112: C450.1, C452.2, JP113.2, R450.1, U225.2, U226.2, U226.4, U226.6
GND113: C454.1, C456.2, JP114.2, R454.1, U227.2, U228.2, U228.4, U228.6
GND114: C458.1, C460.2, JP115.2, R458.1, U229.2, U230.2, U230.4, U230.6
GND115: C462.1, C464.2, JP116.2, R462.1, U231.2, U232.2, U232.4, U232.6
GND116: C466.1, C468.2, JP117.2, R466.1, U233.2, U234.2, U234.4, U234.6
GND117: C470.1, C472.2, JP118.2, R470.1, U235.2, U236.2, U236.4, U236.6
GND118: C474.1, C476.2, JP119.2, R474.1, U237.2, U238.2, U238.4, U238.6
GND119: C478.1, C480.2, JP120.2, R478.1, U239.2, U240.2, U240.4, U240.6
unnamed: C1.1, U2.1
unnamed: C3.1, R3.1, R4.2, U1.4
unnamed: C7.1, U4.1
unnamed: C5.1, R7.1, R8.2, U3.4
unnamed: C7.2, R7.2
unnamed: C1.2, R3.2
unnamed: C2.1, R1.1, R2.2, U1.3
unnamed: C8.1, R5.1, R6.2, U3.3
unnamed: C11.1, U6.1
unnamed: C9.1, R11.1, R12.2, U5.4
unnamed: C11.2, R11.2
unnamed: C12.1, R9.1, R10.2, U5.3
unnamed: C15.1, U8.1
unnamed: C13.1, R15.1, R16.2, U7.4
unnamed: C15.2, R15.2
unnamed: C16.1, R13.1, R14.2, U7.3
unnamed: C19.1, U10.1
unnamed: C17.1, R19.1, R20.2, U9.4
unnamed: C19.2, R19.2
unnamed: C20.1, R17.1, R18.2, U9.3
unnamed: C23.1, U12.1
unnamed: C21.1, R23.1, R24.2, U11.4
unnamed: C23.2, R23.2
unnamed: C24.1, R21.1, R22.2, U11.3
unnamed: C27.1, U14.1
unnamed: C25.1, R27.1, R28.2, U13.4
unnamed: C27.2, R27.2
unnamed: C28.1, R25.1, R26.2, U13.3
unnamed: C31.1, U16.1
unnamed: C29.1, R31.1, R32.2, U15.4
unnamed: C31.2, R31.2
unnamed: C32.1, R29.1, R30.2, U15.3
unnamed: C35.1, U18.1
unnamed: C33.1, R35.1, R36.2, U17.4
unnamed: C35.2, R35.2
unnamed: C36.1, R33.1, R34.2, U17.3
unnamed: C39.1, U20.1
unnamed: C37.1, R39.1, R40.2, U19.4
unnamed: C39.2, R39.2
unnamed: C40.1, R37.1, R38.2, U19.3
unnamed: C43.1, U22.1
unnamed: C41.1, R43.1, R44.2, U21.4
unnamed: C43.2, R43.2
unnamed: C44.1, R41.1, R42.2, U21.3
unnamed: C47.1, U24.1
unnamed: C45.1, R47.1, R48.2, U23.4
unnamed: C47.2, R47.2
unnamed: C48.1, R45.1, R46.2, U23.3
unnamed: C51.1, U26.1
unnamed: C49.1, R51.1, R52.2, U25.4
unnamed: C51.2, R51.2
unnamed: C52.1, R49.1, R50.2, U25.3
unnamed: C55.1, U28.1
unnamed: C53.1, R55.1, R56.2, U27.4
unnamed: C55.2, R55.2
unnamed: C56.1, R53.1, R54.2, U27.3
unnamed: C59.1, U30.1
unnamed: C57.1, R59.1, R60.2, U29.4
unnamed: C59.2, R59.2
unnamed: C60.1, R57.1, R58.2, U29.3
unnamed: C63.1, U32.1
unnamed: C61.1, R63.1, R64.2, U31.4
unnamed: C63.2, R63.2
unnamed: C64.1, R61.1, R62.2, U31.3
unnamed: C67.1, U34.1
unnamed: C65.1, R67.1, R68.2, U33.4
unnamed: C67.2, R67.2
unnamed: C68.1, R65.1, R66.2, U33.3
unnamed: C71.1, U36.1
unnamed: C69.1, R71.1, R72.2, U35.4
unnamed: C71.2, R71.2
unnamed: C72.1, R69.1, R70.2, U35.3
unnamed: C75.1, U38.1
unnamed: C73.1, R75.1, R76.2, U37.4
unnamed: C75.2, R75.2
unnamed: C76.1, R73.1, R74.2, U37.3
unnamed: C79.1, U40.1
unnamed: C77.1, R79.1, R80.2, U39.4
unnamed: C79.2, R79.2
unnamed: C80.1, R77.1, R78.2, U39.3
unnamed: C83.1, U42.1
unnamed: C81.1, R83.1, R84.2, U41.4
unnamed: C83.2, R83.2
unnamed: C84.1, R81.1, R82.2, U41.3
unnamed: C87.1, U44.1
unnamed: C85.1, R87.1, R88.2, U43.4
unnamed: C87.2, R87.2
unnamed: C88.1, R85.1, R86.2, U43.3
unnamed: C91.1, U46.1
unnamed: C89.1, R91.1, R92.2, U45.4
unnamed: C91.2, R91.2
unnamed: C92.1, R89.1, R90.2, U45.3
unnamed: C95.1, U48.1
unnamed: C93.1, R95.1, R96.2, U47.4
unnamed: C95.2, R95.2
unnamed: C96.1, R93.1, R94.2, U47.3
unnamed: C99.1, U50.1
unnamed: C97.1, R99.1, R100.2, U49.4
unnamed: C99.2, R99.2
unnamed: C100.1, R97.1, R98.2, U49.3
unnamed: C103.1, U52.1
unnamed: C101.1, R103.1, R104.2, U51.4
unnamed: C103.2, R103.2
unnamed: C104.1, R101.1, R102.2, U51.3
unnamed: C107.1, U54.1
unnamed: C105.1, R107.1, R108.2, U53.4
unnamed: C107.2, R107.2
unnamed: C108.1, R105.1, R106.2, U53.3
unnamed: C111.1, U56.1
unnamed: C109.1, R111.1, R112.2, U55.4
unnamed: C111.2, R111.2
unnamed: C112.1, R109.1, R110.2, U55.3
unnamed: C115.1, U58.1
unnamed: C113.1, R115.1, R116.2, U57.4
unnamed: C115.2, R115.2
unnamed: C116.1, R113.1, R114.2, U57.3
unnamed: C119.1, U60.1
unnamed: C117.1, R119.1, R120.2, U59.4
unnamed: C119.2, R119.2
unnamed: C120.1, R117.1, R118.2, U59.3
unnamed: C123.1, U62.1
unnamed: C121.1, R123.1, R124.2, U61.4
unnamed: C123.2, R123.2
unnamed: C124.1, R121.1, R122.2, U61.3
unnamed: C127.1, U64.1
unnamed: C125.1, R127.1, R128.2, U63.4
unnamed: C127.2, R127.2
unnamed: C128.1, R125.1, R126.2, U63.3
unnamed: C131.1, U66.1
unnamed: C129.1, R131.1, R132.2, U65.4
unnamed: C131.2, R131.2
unnamed: C132.1, R129.1, R130.2, U65.3
unnamed: C135.1, U68.1
unnamed: C133.1, R135.1, R136.2, U67.4
unnamed: C135.2, R135.2
unnamed: C136.1, R133.1, R134.2, U67.3
unnamed: C139.1, U70.1
unnamed: C137.1, R139.1, R140.2, U69.4
unnamed: C139.2, R139.2
unnamed: C140.1, R137.1, R138.2, U69.3
unnamed: C143.1, U72.1
unnamed: C141.1, R143.1, R144.2, U71.4
unnamed: C143.2, R143.2
unnamed: C144.1, R141.1, R142.2, U71.3
unnamed: C147.1, U74.1
unnamed: C145.1, R147.1, R148.2, U73.4
unnamed: C147.2, R147.2
unnamed: C148.1, R145.1, R146.2, U73.3
unnamed: C151.1, U76.1
unnamed: C149.1, R151.1, R152.2, U75.4
unnamed: C151.2, R151.2
unnamed: C152.1, R149.1, R150.2, U75.3
unnamed: C155.1, U78.1
unnamed: C153.1, R155.1, R156.2, U77.4
unnamed: C155.2, R155.2
unnamed: C156.1, R153.1, R154.2, U77.3
unnamed: C159.1, U80.1
unnamed: C157.1, R159.1, R160.2, U79.4
unnamed: C159.2, R159.2
unnamed: C160.1, R157.1, R158.2, U79.3
unnamed: C163.1, U82.1
unnamed: C161.1, R163.1, R164.2, U81.4
unnamed: C163.2, R163.2
unnamed: C164.1, R161.1, R162.2, U81.3
unnamed: C167.1, U84.1
unnamed: C165.1, R167.1, R168.2, U83.4
unnamed: C167.2, R167.2
unnamed: C168.1, R165.1, R166.2, U83.3
unnamed: C171.1, U86.1
unnamed: C169.1, R171.1, R172.2, U85.4
unnamed: C171.2, R171.2
unnamed: C172.1, R169.1, R170.2, U85.3
unnamed: C175.1, U88.1
unnamed: C173.1, R175.1, R176.2, U87.4
unnamed: C175.2, R175.2
unnamed: C176.1, R173.1, R174.2, U87.3
unnamed: C179.1, U90.1
unnamed: C177.1, R179.1, R180.2, U89.4
unnamed: C179.2, R179.2
unnamed: C180.1, R177.1, R178.2, U89.3
unnamed: C183.1, U92.1
unnamed: C181.1, R183.1, R184.2, U91.4
unnamed: C183.2, R183.2
unnamed: C184.1, R181.1, R182.2, U91.3
unnamed: C187.1, U94.1
unnamed: C185.1, R187.1, R188.2, U93.4
unnamed: C187.2, R187.2
unnamed: C188.1, R185.1, R186.2, U93.3
unnamed: C191.1, U96.1
unnamed: C189.1, R191.1, R192.2, U95.4
unnamed: C191.2, R191.2
unnamed: C192.1, R189.1, R190.2, U95.3
unnamed: C195.1, U98.1
unnamed: C193.1, R195.1, R196.2, U97.4
unnamed: C195.2, R195.2
unnamed: C196.1, R193.1, R194.2, U97.3
unnamed: C199.1, U100.1
unnamed: C197.1, R199.1, R200.2, U99.4
unnamed: C199.2, R199.2
unnamed: C200.1, R197.1, R198.2, U99.3
unnamed: C203.1, U102.1
unnamed: C201.1, R203.1, R204.2, U101.4
unnamed: C203.2, R203.2
unnamed: C204.1, R201.1, R202.2, U101.3
unnamed: C207.1, U104.1
unnamed: C205.1, R207.1, R208.2, U103.4
unnamed: C207.2, R207.2
unnamed: C208.1, R205.1, R206.2, U103.3
unnamed: C211.1, U106.1
unnamed: C209.1, R211.1, R212.2, U105.4
unnamed: C211.2, R211.2
unnamed: C212.1, R209.1, R210.2, U105.3
unnamed: C215.1, U108.1
unnamed: C213.1, R215.1, R216.2, U107.4
unnamed: C215.2, R215.2
unnamed: C216.1, R213.1, R214.2, U107.3
unnamed: C219.1, U110.1
unnamed: C217.1, R219.1, R220.2, U109.4
unnamed: C219.2, R219.2
unnamed: C220.1, R217.1, R218.2, U109.3
unnamed: C223.1, U112.1
unnamed: C221.1, R223.1, R224.2, U111.4
unnamed: C223.2, R223.2
unnamed: C224.1, R221.1, R222.2, U111.3
unnamed: C227.1, U114.1
unnamed: C225.1, R227.1, R228.2, U113.4
unnamed: C227.2, R227.2
unnamed: C228.1, R225.1, R226.2, U113.3
unnamed: C231.1, U116.1
unnamed: C229.1, R231.1, R232.2, U115.4
unnamed: C231.2, R231.2
unnamed: C232.1, R229.1, R230.2, U115.3
unnamed: C235.1, U118.1
unnamed: C233.1, R235.1, R236.2, U117.4
unnamed: C235.2, R235.2
unnamed: C236.1, R233.1, R234.2, U117.3
unnamed: C239.1, U120.1
unnamed: C237.1, R239.1, R240.2, U119.4
unnamed: C239.2, R239.2
unnamed: C240.1, R237.1, R238.2, U119.3
unnamed: C243.1, U122.1
unnamed: C241.1, R243.1, R244.2, U121.4
unnamed: C243.2, R243.2
unnamed: C244.1, R241.1, R242.2, U121.3
unnamed: C247.1, U124.1
unnamed: C245.1, R247.1, R248.2, U123.4
unnamed: C247.2, R247.2
unnamed: C248.1, R245.1, R246.2, U123.3
unnamed: C251.1, U126.1
unnamed: C249.1, R251.1, R252.2, U125.4
unnamed: C251.2, R251.2
unnamed: C252.1, R249.1, R250.2, U125.3
unnamed: C255.1, U128.1
unnamed: C253.1, R255.1, R256.2, U127.4
unnamed: C255.2, R255.2
unnamed: C256.1, R253.1, R254.2, U127.3
unnamed: C259.1, U130.1
unnamed: C257.1, R259.1, R260.2, U129.4
unnamed: C259.2, R259.2
unnamed: C260.1, R257.1, R258.2, U129.3
unnamed: C263.1, U132.1
unnamed: C261.1, R263.1, R264.2, U131.4
unnamed: C263.2, R263.2
unnamed: C264.1, R261.1, R262.2, U131.3
unnamed: C267.1, U134.1
unnamed: C265.1, R267.1, R268.2, U133.4
unnamed: C267.2, R267.2
unnamed: C268.1, R265.1, R266.2, U133.3
unnamed: C271.1, U136.1
unnamed: C269.1, R271.1, R272.2, U135.4
unnamed: C271.2, R271.2
unnamed: C272.1, R269.1, R270.2, U135.3
unnamed: C275.1, U138.1
unnamed: C273.1, R275.1, R276.2, U137.4
unnamed: C275.2, R275.2
unnamed: C276.1, R273.1, R274.2, U137.3
unnamed: C279.1, U140.1
unnamed: C277.1, R279.1, R280.2, U139.4
unnamed: C279.2, R279.2
unnamed: C280.1, R277.1, R278.2, U139.3
unnamed: C283.1, U142.1
unnamed: C281.1, R283.1, R284.2, U141.4
unnamed: C283.2, R283.2
unnamed: C284.1, R281.1, R282.2, U141.3
unnamed: C287.1, U144.1
unnamed: C285.1, R287.1, R288.2, U143.4
unnamed: C287.2, R287.2
unnamed: C288.1, R285.1, R286.2, U143.3
unnamed: C291.1, U146.1
unnamed: C289.1, R291.1, R292.2, U145.4
unnamed: C291.2, R291.2
unnamed: C292.1, R289.1, R290.2, U145.3
unnamed: C295.1, U148.1
unnamed: C293.1, R295.1, R296.2, U147.4
unnamed: C295.2, R295.2
unnamed: C296.1, R293.1, R294.2, U147.3
unnamed: C299.1, U150.1
unnamed: C297.1, R299.1, R300.2, U149.4
unnamed: C299.2, R299.2
unnamed: C300.1, R297.1, R298.2, U149.3
unnamed: C303.1, U152.1
unnamed: C301.1, R303.1, R304.2, U151.4
unnamed: C303.2, R303.2
unnamed: C304.1, R301.1, R302.2, U151.3
unnamed: C307.1, U154.1
unnamed: C305.1, R307.1, R308.2, U153.4
unnamed: C307.2, R307.2
unnamed: C308.1, R305.1, R306.2, U153.3
unnamed: C311.1, U156.1
unnamed: C309.1, R311.1, R312.2, U155.4
unnamed: C311.2, R311.2
unnamed: C312.1, R309.1, R310.2, U155.3
unnamed: C315.1, U158.1
unnamed: C313.1, R315.1, R316.2, U157.4
unnamed: C315.2, R315.2
unnamed: C316.1, R313.1, R314.2, U157.3
unnamed: C319.1, U160.1
unnamed: C317.1, R319.1, R320.2, U159.4
unnamed: C319.2, R319.2
unnamed: C320.1, R317.1, R318.2, U159.3
unnamed: C323.1, U162.1
unnamed: C321.1, R323.1, R324.2, U161.4
unnamed: C323.2, R323.2
unnamed: C324.1, R321.1, R322.2, U161.3
unnamed: C327.1, U164.1
unnamed: C325.1, R327.1, R328.2, U163.4
unnamed: C327.2, R327.2
unnamed: C328.1, R325.1, R326.2, U163.3
unnamed: C331.1, U166.1
unnamed: C329.1, R331.1, R332.2, U165.4
unnamed: C331.2, R331.2
unnamed: C332.1, R329.1, R330.2, U165.3
unnamed: C335.1, U168.1
unnamed: C333.1, R335.1, R336.2, U167.4
unnamed: C335.2, R335.2
unnamed: C336.1, R333.1, R334.2, U167.3
unnamed: C339.1, U170.1
unnamed: C337.1, R339.1, R340.2, U169.4
unnamed: C339.2, R339.2
unnamed: C340.1, R337.1, R338.2, U169.3
unnamed: C343.1, U172.1
unnamed: C341.1, R343.1, R344.2, U171.4
unnamed: C343.2, R343.2
unnamed: C344.1, R341.1, R342.2, U171.3
unnamed: C347.1, U174.1
unnamed: C345.1, R347.1, R348.2, U173.4
unnamed: C347.2, R347.2
unnamed: C348.1, R345.1, R346.2, U173.3
unnamed: C351.1, U176.1
unnamed: C349.1, R351.1, R352.2, U175.4
unnamed: C351.2, R351.2
unnamed: C352.1, R349.1, R350.2, U175.3
unnamed: C355.1, U178.1
unnamed: C353.1, R355.1, R356.2, U177.4
unnamed: C355.2, R355.2
unnamed: C356.1, R353.1, R354.2, U177.3
unnamed: C359.1, U180.1
unnamed: C357.1, R359.1, R360.2, U179.4
unnamed: C359.2, R359.2
unnamed: C360.1, R357.1, R358.2, U179.3
unnamed: C363.1, U182.1
unnamed: C361.1, R363.1, R364.2, U181.4
unnamed: C363.2, R363.2
unnamed: C364.1, R361.1, R362.2, U181.3
unnamed: C367.1, U184.1
unnamed: C365.1, R367.1, R368.2, U183.4
unnamed: C367.2, R367.2
unnamed: C368.1, R365.1, R366.2, U183.3
unnamed: C371.1, U186.1
unnamed: C369.1, R371.1, R372.2, U185.4
unnamed: C371.2, R371.2
unnamed: C372.1, R369.1, R370.2, U185.3
unnamed: C375.1, U188.1
unnamed: C373.1, R375.1, R376.2, U187.4
unnamed: C375.2, R375.2
unnamed: C376.1, R373.1, R374.2, U187.3
unnamed: C379.1, U190.1
unnamed: C377.1, R379.1, R380.2, U189.4
unnamed: C379.2, R379.2
unnamed: C380.1, R377.1, R378.2, U189.3
unnamed: C383.1, U192.1
unnamed: C381.1, R383.1, R384.2, U191.4
unnamed: C383.2, R383.2
unnamed: C384.1, R381.1, R382.2, U191.3
unnamed: C387.1, U194.1
unnamed: C385.1, R387.1, R388.2, U193.4
unnamed: C387.2, R387.2
unnamed: C388.1, R385.1, R386.2, U193.3
unnamed: C391.1, U196.1
unnamed: C389.1, R391.1, R392.2, U195.4
unnamed: C391.2, R391.2
unnamed: C392.1, R389.1, R390.2, U195.3
unnamed: C395.1, U198.1
unnamed: C393.1, R395.1, R396.2, U197.4
unnamed: C395.2, R395.2
unnamed: C396.1, R393.1, R394.2, U197.3
unnamed: C399.1, U200.1
unnamed: C397.1, R399.1, R400.2, U199.4
unnamed: C399.2, R399.2
unnamed: C400.1, R397.1, R398.2, U199.3
unnamed: C403.1, U202.1
unnamed: C401.1, R403.1, R404.2, U201.4
unnamed: C403.2, R403.2
unnamed: C404.1, R401.1, R402.2, U201.3
unnamed: C407.1, U204.1
unnamed: C405.1, R407.1, R408.2, U203.4
unnamed: C407.2, R407.2
unnamed: C408.1, R405.1, R406.2, U203.3
unnamed: C411.1, U206.1
unnamed: C409.1, R411.1, R412.2, U205.4
unnamed: C411.2, R411.2
unnamed: C412.1, R409.1, R410.2, U205.3
unnamed: C415.1, U208.1
unnamed: C413.1, R415.1, R416.2, U207.4
unnamed: C415.2, R415.2
unnamed: C416.1, R413.1, R414.2, U207.3
unnamed: C419.1, U210.1
unnamed: C417.1, R419.1, R420.2, U209.4
unnamed: C419.2, R419.2
unnamed: C420.1, R417.1, R418.2, U209.3
unnamed: C423.1, U212.1
unnamed: C421.1, R423.1, R424.2, U211.4
unnamed: C423.2, R423.2
unnamed: C424.1, R421.1, R422.2, U211.3
unnamed: C427.1, U214.1
unnamed: C425.1, R427.1, R428.2, U213.4
unnamed: C427.2, R427.2
unnamed: C428.1, R425.1, R426.2, U213.3
unnamed: C431.1, U216.1
unnamed: C429.1, R431.1, R432.2, U215.4
unnamed: C431.2, R431.2
unnamed: C432.1, R429.1, R430.2, U215.3
unnamed: C435.1, U218.1
unnamed: C433.1, R435.1, R436.2, U217.4
unnamed: C435.2, R435.2
unnamed: C436.1, R433.1, R434.2, U217.3
unnamed: C439.1, U220.1
unnamed: C437.1, R439.1, R440.2, U219.4
unnamed: C439.2, R439.2
unnamed: C440.1, R437.1, R438.2, U219.3
unnamed: C443.1, U222.1
unnamed: C441.1, R443.1, R444.2, U221.4
unnamed: C443.2, R443.2
unnamed: C444.1, R441.1, R442.2, U221.3
unnamed: C447.1, U224.1
unnamed: C445.1, R447.1, R448.2, U223.4
unnamed: C447.2, R447.2
unnamed: C448.1, R445.1, R446.2, U223.3
unnamed: C451.1, U226.1
unnamed: C449.1, R451.1, R452.2, U225.4
unnamed: C451.2, R451.2
unnamed: C452.1, R449.1, R450.2, U225.3
unnamed: C455.1, U228.1
unnamed: C453.1, R455.1, R456.2, U227.4
unnamed: C455.2, R455.2
unnamed: C456.1, R453.1, R454.2, U227.3
unnamed: C459.1, U230.1
unnamed: C457.1, R459.1, R460.2, U229.4
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
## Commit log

2015-02-03 Initial hardware/firmware commit
2015-10-15 larger panel v13

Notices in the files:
parts and their libraries:
SparkFun: Released under the Creative Commons Attribution Share-Alike 3.0 License
SparkFun: http://creativecommons.org/licenses/by-sa/3.0
SparkFun-Aesthetics: Licensing: Creative Commons ShareAlike 4.0 International - https://creativecommons.org/licenses/by-sa/4.0
